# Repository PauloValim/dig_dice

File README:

Dado Digital usando CI´s da família TTL 74LS

A ideia deste projeto é servir como apoio às aulas da disciplina de circuitos digitais. Ao longo da disciplina, cada um dos blocos que compõem o dado digital será apresentado, de forma que, ao final, o aluno tenha um produto real e, além disso, tenha total entendimento de todos os detalhes do projeto.

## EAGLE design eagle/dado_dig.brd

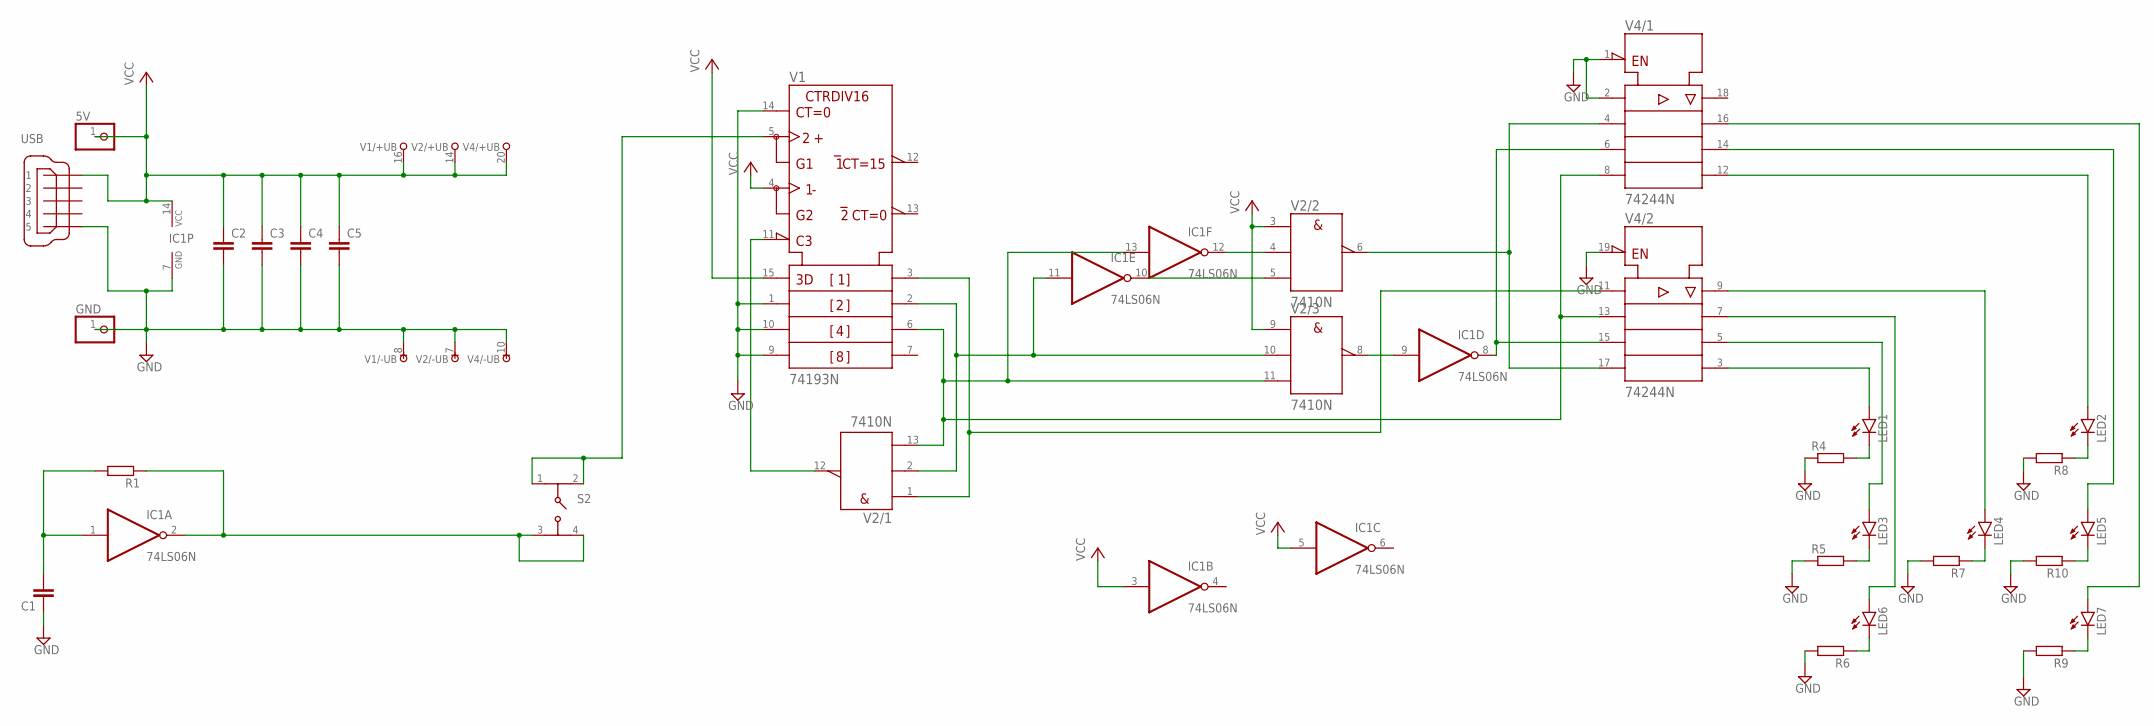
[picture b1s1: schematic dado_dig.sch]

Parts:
5V: PINHD-1X1; 1X01
C1, C2, C3, C4, C5: C-EUC0805K; C0805K
GND: PINHD-1X1; 1X01
IC1: 74LS06N; DIL14
LED1, LED2, LED3, LED4, LED5, LED6, LED7: LED5MM
R1, R4, R5, R6, R7, R8, R9, R10: R-EU_M0805; M0805
S2: 430456073736
USB: MINI-USB-32005-301; 32005-301
V1: 74193N; DIL16
V2: 7410N; DIL14
V4: 74244N; DIL20

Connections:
GND: C1.1, C2.2, C3.2, C4.2, C5.2, GND.1, IC1.7 (GND), R4.1, R5.1, R6.2, R7.2, R8.2, R9.2, R10.2, USB.5, V1.1 (B), V1.8 (-UB), V1.9 (D), V1.10 (C), V1.14 (CLR), V2.7 (-UB), V4.1 (!G), V4.2 (A1), V4.10 (-UB), V4.19 (!G)
unnamed: IC1.13 (I), V1.6 (QC), V2.11 (C), V2.13 (C), V4.8 (A4), V4.13 (A2)
unnamed: IC1.9 (I), V2.8 (Y)
unnamed: C1.2, IC1.1 (I), R1.2
unnamed: IC1.12 (O), V2.4 (B)
unnamed: IC1.2 (O), R1.1, S2.3 (2), S2.4
unnamed: V1.3 (QA), V2.1 (A), V4.11 (A1)
unnamed: IC1.10 (O), V2.5 (C)
unnamed: S2.1, S2.2 (3), V1.5 (UP)
unnamed: IC1.11 (I), V1.2 (QB), V2.2 (B), V2.10 (B)
unnamed: LED6.K (C), R6.1
unnamed: LED4.A, V4.9 (Y1)
unnamed: LED5.K (C), R10.1
unnamed: LED3.K (C), R5.2
unnamed: LED5.A, V4.14 (Y3)
unnamed: LED1.A, V4.3 (Y4)
unnamed: LED4.K (C), R7.1
unnamed: LED2.A, V4.12 (Y4)
unnamed: LED2.K (C), R8.1
unnamed: LED7.K (C), R9.1
unnamed: LED1.K (C), R4.2
unnamed: LED7.A, V4.16 (Y2)
unnamed: V1.11 (!LOAD), V2.12 (Y)
unnamed: LED6.A, V4.7 (Y2)
unnamed: V2.6 (Y), V4.4 (A2), V4.17 (A4)
unnamed: LED3.A, V4.5 (Y3)
unnamed: IC1.8 (O), V4.6 (A3), V4.15 (A3)
VCC: 5V.1, C2.1, C3.1, C4.1, C5.1, IC1.3 (I), IC1.5 (I), IC1.14 (VCC), USB.1, V1.4 (DOWN), V1.15 (A), V1.16 (+UB), V2.3 (A), V2.9 (A), V2.14 (+UB), V4.20 (+UB)

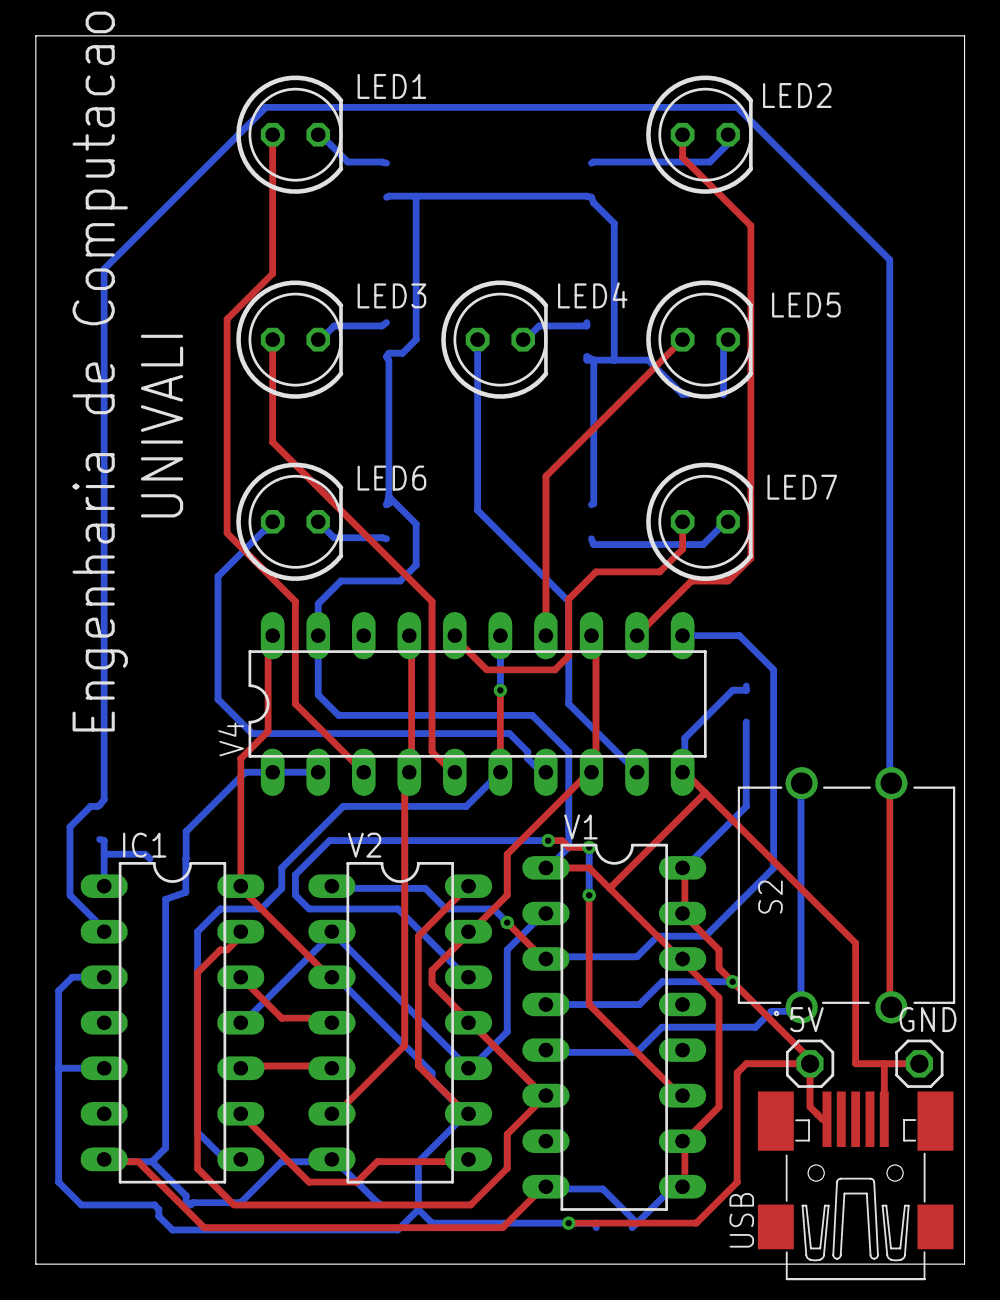
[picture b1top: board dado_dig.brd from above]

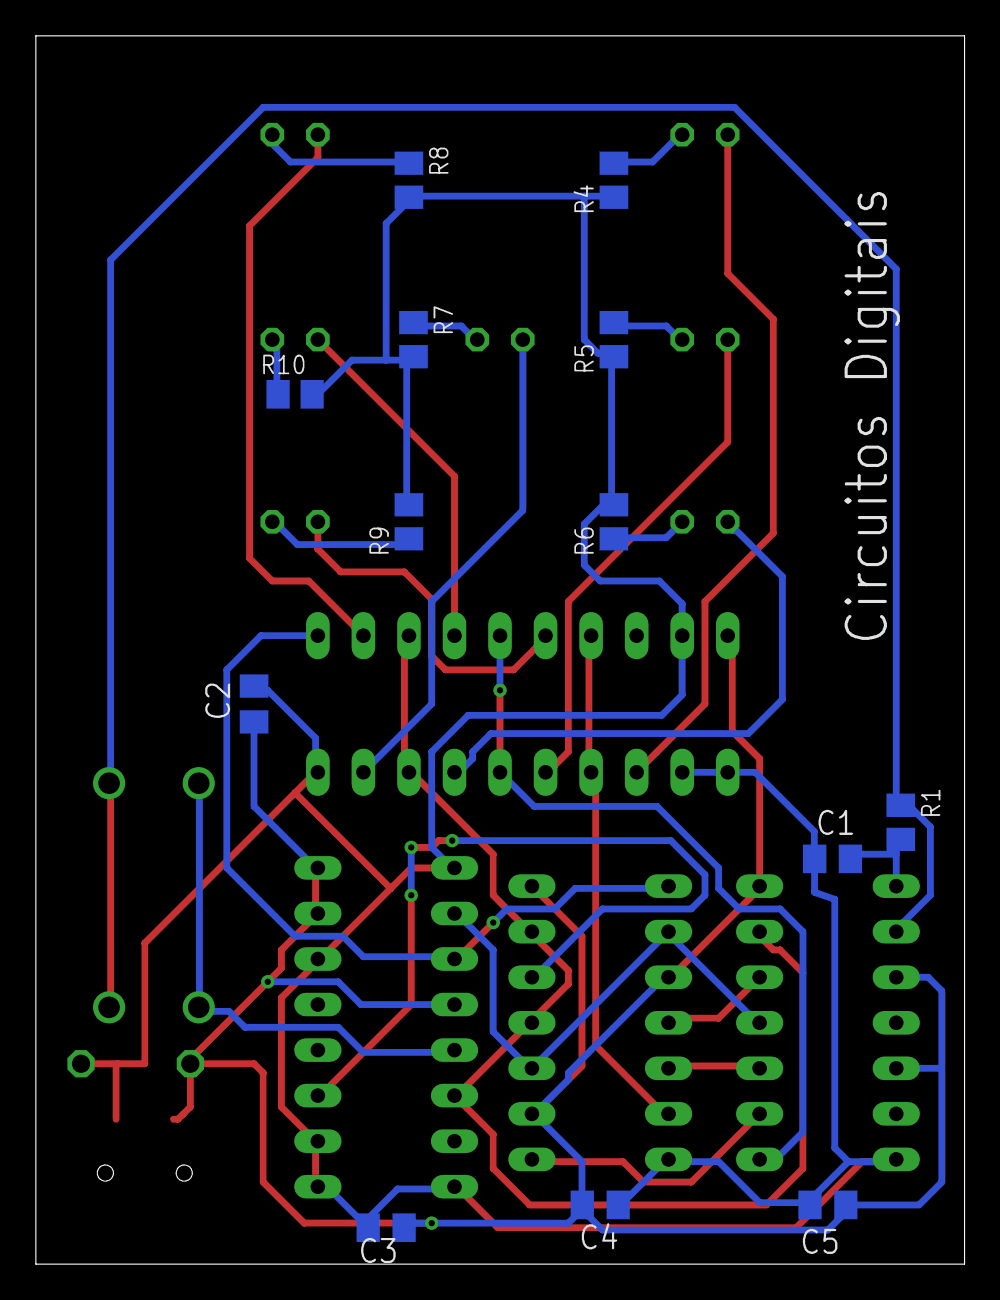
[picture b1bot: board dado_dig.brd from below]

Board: 2 copper layers, 51.8 x 68.5 mm, 28 parts (13 on the bottom side), 28 nets.

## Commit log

2020-01-29 versao inicial do projeto
2020-01-29 adicionado arquivo README
2020-02-26 inclusao lista material
2020-03-26 documento com descricao
    documento com a descricao baseada em diagrama de blocos
